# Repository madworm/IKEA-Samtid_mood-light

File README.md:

IKEA-Samtid_mood-light
======================

LAYOUT FILES: Circular extension board for IKEA Samtid lamps (*).

WS2812B-based Arduino compatible RGB ring light. 

Remote control with:

* HC-05 bluetooth module (native).
* ESP8266 with adapter PCB & 3.3V regulator (small adapter).

Hardware releases: 

* [V0.27.a](https://github.com/madworm/IKEA-Samtid_mood-light/releases/tag/V0.27.a): basic mood light
* [Final](https://github.com/madworm/IKEA-Samtid_mood-light/releases/tag/Final): upgraded with Bluetooth/WiFi option

See 'Docs' on master branch for hints/errata!

Firmware [repository](https://github.com/madworm/IKEA-Samtid_mood-light_FW) & Arduino setup files.
Works with Adafruit [NeoPixel](https://github.com/adafruit/Adafruit_NeoPixel) library.

(*) I was told it also works with IKEA Aläng lamps.

---

Created with KiCad BZR5093 or later. You need an up-to-date release to open these files!

Before having PC-boards made, please make sure you know about your manufacturer's peculiarities!
Especially drill-sizes and their tolerances may vary too much and give you trouble.

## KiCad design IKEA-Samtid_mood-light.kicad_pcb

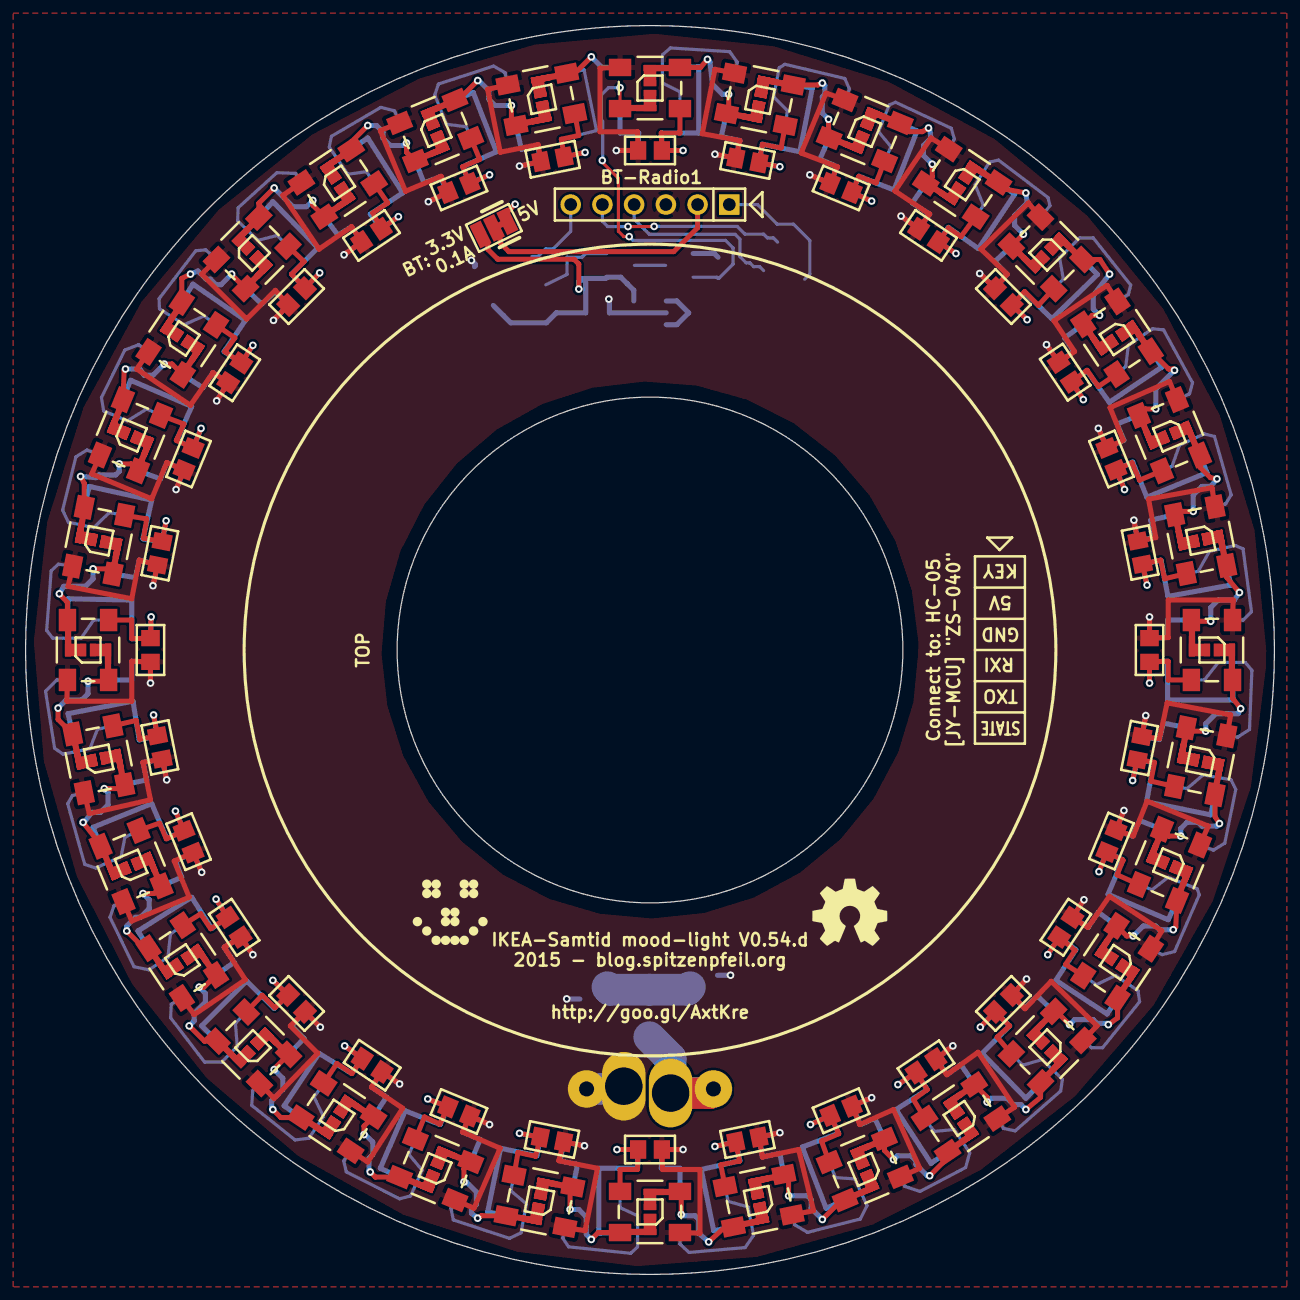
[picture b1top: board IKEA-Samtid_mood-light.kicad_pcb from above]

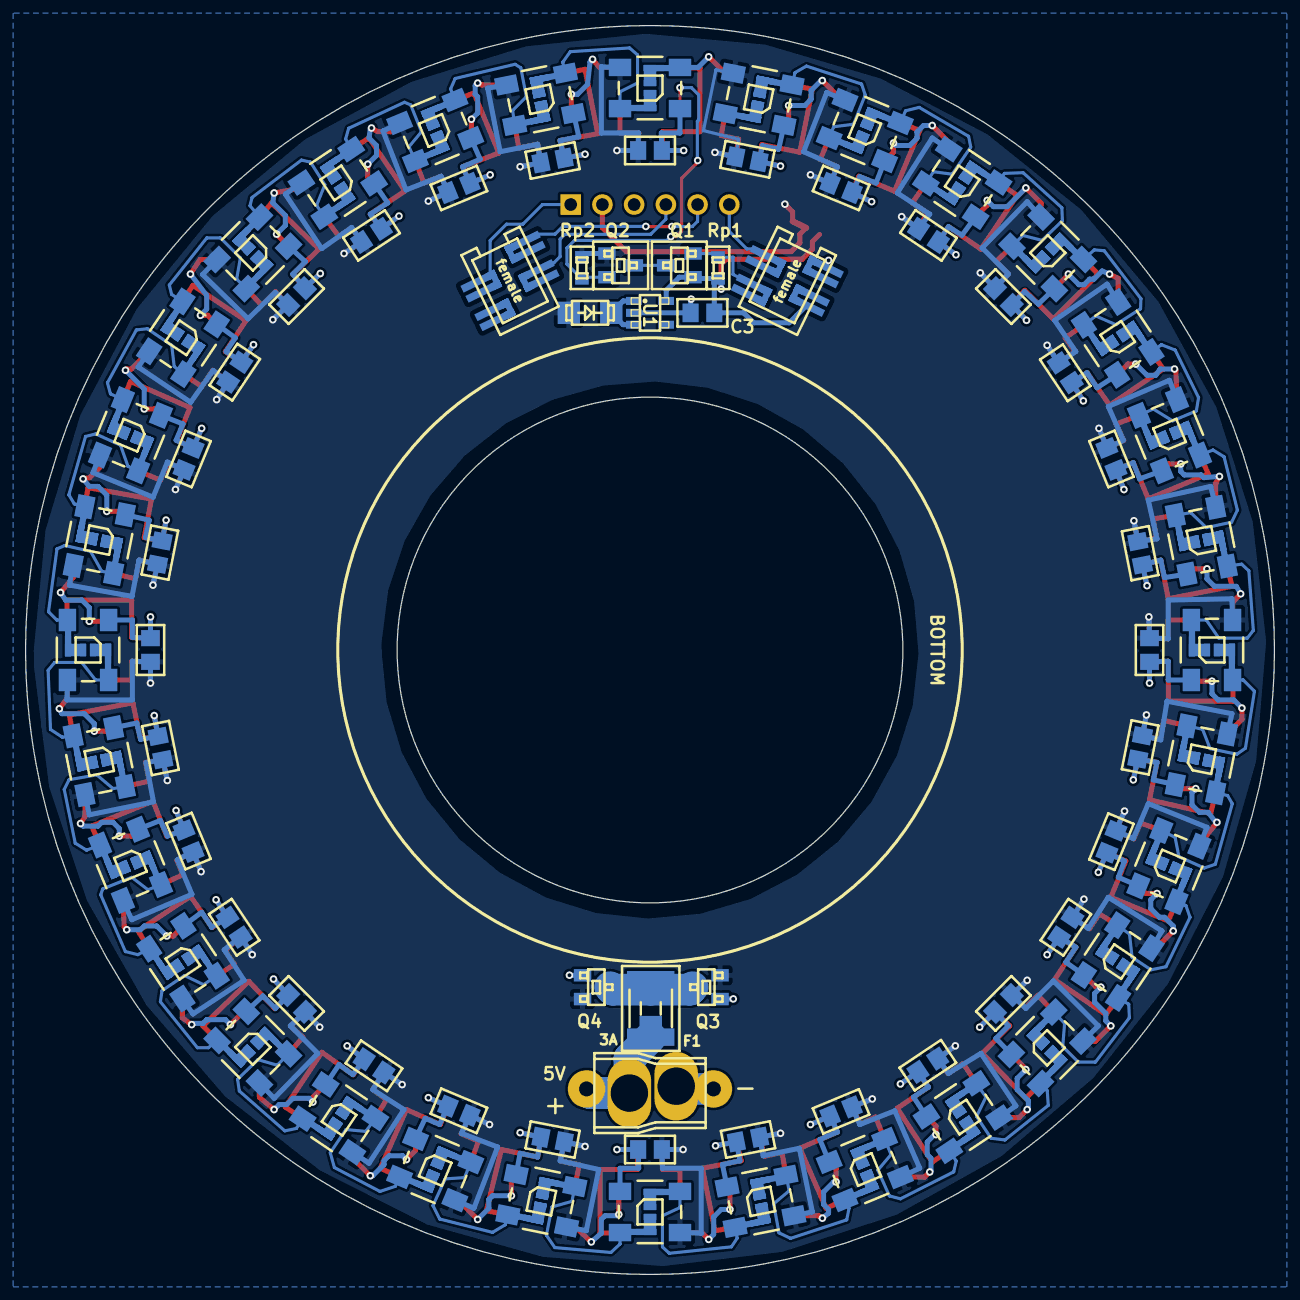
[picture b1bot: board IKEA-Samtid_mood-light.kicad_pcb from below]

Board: 2 copper layers, 100.0 x 100.0 mm, 146 parts (77 on the bottom side), 77 nets.

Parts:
BT-Radio1: HC-05; SIL-6
C3, C5, C6, C7, C8, C9, C10, C11, C12, C13, C14, C15, C16, C17, C18, C19, C20, C21, C22, C23, C24, C25, C26, C27, C28, C29, C30, C31, C32, C33, C34, C35, C36, C37, C38, C39, C40, C41, C42, C43, C44, C45, C46, C47, C48, C49, C50, C51, C52, C53, C54, C55, C56, C57, C58, C59, C60, C61, C62, C63, C64, C65, C66, C67, C68: 1µF; MADW__C0805
DS1: SS14L; MADW__diode_sub-SMA
F1: 3A-poly; SM1812_1206
JP3: BT:5V(3.3); SMD-solder-bridge-3pin
LED1, LED2, LED3, LED4, LED5, LED6, LED7, LED8, LED9, LED10, LED11, LED12, LED13, LED14, LED15, LED16, LED17, LED18, LED19, LED20, LED21, LED22, LED23, LED24, LED25, LED26, LED27, LED28, LED29, LED30, LED31, LED32, LED33, LED34, LED35, LED36, LED37, LED38, LED39, LED40, LED41, LED42, LED43, LED44, LED45, LED46, LED47, LED48, LED49, LED50, LED51, LED52, LED53, LED54, LED55, LED56, LED57, LED58, LED59, LED60, LED61, LED62, LED63, LED64: WS2812B; WS2812B_data-bridgeable
LOGO1: LED_smile_silkscreen_6mm
LOGO2: OSHW-logo_silkscreen_6mm
P2: POWER; Deans_mini-T_male
P3: POWER; Socket_MOLEX-KK-RM2-54mm_Lock_5pin_straight
P3.1: B-to-B-1A; 0-188275-4_SMD_4-pin_female_split-pads
P4.1: B-to-B-2A; 0-188275-4_SMD_4-pin_female_split-pads
Q1, Q2: BSS138; MADW__SOT23
Q3, Q4: IRLML6401PbF; MADW__SOT23
Rp1, Rp2: 1k5; MADW__R0603_2
U1: AP2204K-SOT23-5; MADW__SOT23-5

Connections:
+5V: C5.1, C6.1, C7.1, C8.1, C9.1, C10.1, C11.1, C12.1, C13.1, C14.1, C15.1, C16.1, C17.1, C18.1, C19.1, C20.1, C21.1, C22.1, C23.1, C24.1, C25.1, C26.1, C27.1, C28.1, C29.1, C30.1, C31.1, C32.1, C33.1, C34.1, C35.1, C36.1, C37.1, C38.1, C39.1, C40.1, C41.1, C42.1, C43.1, C44.1, C45.1, C46.1, C47.1, C48.1, C49.1, C50.1, C51.1, C52.1, C53.1, C54.1, C55.1, C56.1, C57.1, C58.1, C59.1, C60.1, C61.1, C62.1, C63.1, C64.1, C65.1, C66.1, C67.1, C68.1, DS1.1, JP3.1, LED1.1, LED2.1, LED3.1, LED4.1, LED5.1, LED6.1, LED7.1, LED8.1, LED9.1, LED10.1, LED11.1, LED12.1, LED13.1, LED14.1, LED15.1, LED16.1, LED17.1, LED18.1, LED19.1, LED20.1, LED21.1, LED22.1, LED23.1, LED24.1, LED25.1, LED26.1, LED27.1, LED28.1, LED29.1, LED30.1, LED31.1, LED32.1, LED33.1, LED34.1, LED35.1, LED36.1, LED37.1, LED38.1, LED39.1, LED40.1, LED41.1, LED42.1, LED43.1, LED44.1, LED45.1, LED46.1, LED47.1, LED48.1, LED49.1, LED50.1, LED51.1, LED52.1, LED53.1, LED54.1, LED55.1, LED56.1, LED57.1, LED58.1, LED59.1, LED60.1, LED61.1, LED62.1, LED63.1, LED64.1, Q2.1, Q3.2, Q4.2, Rp2.1
/5V_raw: F1.2, P2.2, P3.5
/KEY.A: BT-Radio1.1, P4.1.2
/LEDS.A: P3.1.4, Q1.2, Rp1.2
/RXI.A: BT-Radio1.4, P4.1.3
/STATE.A: BT-Radio1.6, P3.1.2
/TXO.A: BT-Radio1.5, P4.1.1
/VCC.A: C3.1, JP3.3, P3.1.3, Q1.1, Rp1.1, U1.5
/WS2812B-LEDs-1/A_IN: LED1.4, Q2.2, Rp2.2
/WS2812B-LEDs-1/A_OUT: LED8.2, LED9.4
/WS2812B-LEDs-1/B_OUT: LED16.2, LED17.4
/WS2812B-LEDs-1/C_OUT: LED24.2, LED25.4
/WS2812B-LEDs-1/D_OUT: LED32.2, LED33.4
/WS2812B-LEDs-1/GND: BT-Radio1.3, C3.2, C5.2, C6.2, C7.2, C8.2, C9.2, C10.2, C11.2, C12.2, C13.2, C14.2, C15.2, C16.2, C17.2, C18.2, C19.2, C20.2, C21.2, C22.2, C23.2, C24.2, C25.2, C26.2, C27.2, C28.2, C29.2, C30.2, C31.2, C32.2, C33.2, C34.2, C35.2, C36.2, C37.2, C38.2, C39.2, C40.2, C41.2, C42.2, C43.2, C44.2, C45.2, C46.2, C47.2, C48.2, C49.2, C50.2, C51.2, C52.2, C53.2, C54.2, C55.2, C56.2, C57.2, C58.2, C59.2, C60.2, C61.2, C62.2, C63.2, C64.2, C65.2, C66.2, C67.2, C68.2, LED1.3, LED2.3, LED3.3, LED4.3, LED5.3, LED6.3, LED7.3, LED8.3, LED9.3, LED10.3, LED11.3, LED12.3, LED13.3, LED14.3, LED15.3, LED16.3, LED17.3, LED18.3, LED19.3, LED20.3, LED21.3, LED22.3, LED23.3, LED24.3, LED25.3, LED26.3, LED27.3, LED28.3, LED29.3, LED30.3, LED31.3, LED32.3, LED33.3, LED34.3, LED35.3, LED36.3, LED37.3, LED38.3, LED39.3, LED40.3, LED41.3, LED42.3, LED43.3, LED44.3, LED45.3, LED46.3, LED47.3, LED48.3, LED49.3, LED50.3, LED51.3, LED52.3, LED53.3, LED54.3, LED55.3, LED56.3, LED57.3, LED58.3, LED59.3, LED60.3, LED61.3, LED62.3, LED63.3, LED64.3, P2.1, P3.1, P3.1.1, Q3.1, Q4.1, U1.2
/WS2812B-LEDs-2/E_OUT: LED40.2, LED41.4
/WS2812B-LEDs-2/F_OUT: LED48.2, LED49.4
/WS2812B-LEDs-2/G_OUT: LED56.2, LED57.4
unnamed: BT-Radio1.2, JP3.2
unnamed: DS1.2, U1.1, U1.3
unnamed: F1.1, Q3.3, Q4.3
unnamed: LED1.2, LED2.4
unnamed: LED2.2, LED3.4
unnamed: LED3.2, LED4.4
unnamed: LED4.2, LED5.4
unnamed: LED5.2, LED6.4
unnamed: LED6.2, LED7.4
unnamed: LED7.2, LED8.4
unnamed: LED10.2, LED11.4
unnamed: LED9.2, LED10.4
unnamed: LED11.2, LED12.4
unnamed: LED12.2, LED13.4
unnamed: LED13.2, LED14.4
unnamed: LED14.2, LED15.4
unnamed: LED15.2, LED16.4
unnamed: LED17.2, LED18.4
unnamed: LED18.2, LED19.4
unnamed: LED19.2, LED20.4
unnamed: LED20.2, LED21.4
unnamed: LED21.2, LED22.4
unnamed: LED22.2, LED23.4
unnamed: LED23.2, LED24.4
unnamed: LED25.2, LED26.4
unnamed: LED26.2, LED27.4
unnamed: LED27.2, LED28.4
unnamed: LED28.2, LED29.4
unnamed: LED29.2, LED30.4
unnamed: LED30.2, LED31.4
unnamed: LED31.2, LED32.4
unnamed: LED33.2, LED34.4
unnamed: LED34.2, LED35.4
unnamed: LED35.2, LED36.4
unnamed: LED36.2, LED37.4
unnamed: LED37.2, LED38.4
unnamed: LED38.2, LED39.4
unnamed: LED39.2, LED40.4
unnamed: LED41.2, LED42.4
unnamed: LED42.2, LED43.4
unnamed: LED43.2, LED44.4
unnamed: LED44.2, LED45.4
unnamed: LED45.2, LED46.4
unnamed: LED46.2, LED47.4
unnamed: LED47.2, LED48.4
unnamed: LED49.2, LED50.4
unnamed: LED50.2, LED51.4
unnamed: LED51.2, LED52.4
unnamed: LED52.2, LED53.4
unnamed: LED53.2, LED54.4
unnamed: LED54.2, LED55.4
unnamed: LED55.2, LED56.4
unnamed: LED57.2, LED58.4
unnamed: LED58.2, LED59.4
unnamed: LED59.2, LED60.4
unnamed: LED60.2, LED61.4
unnamed: LED61.2, LED62.4
unnamed: LED62.2, LED63.4
unnamed: LED63.2, LED64.4
unnamed: Q1.3, Q2.3

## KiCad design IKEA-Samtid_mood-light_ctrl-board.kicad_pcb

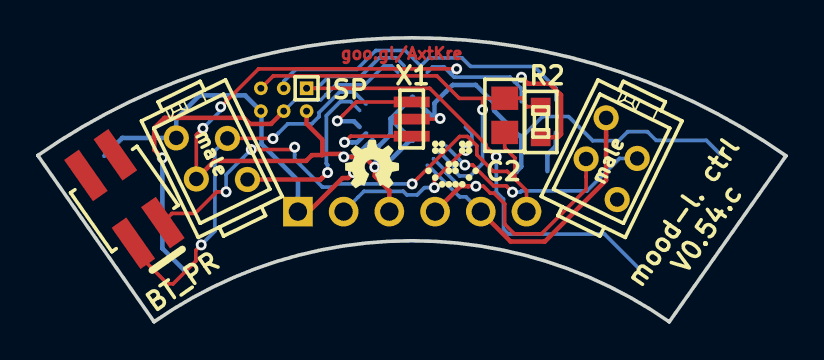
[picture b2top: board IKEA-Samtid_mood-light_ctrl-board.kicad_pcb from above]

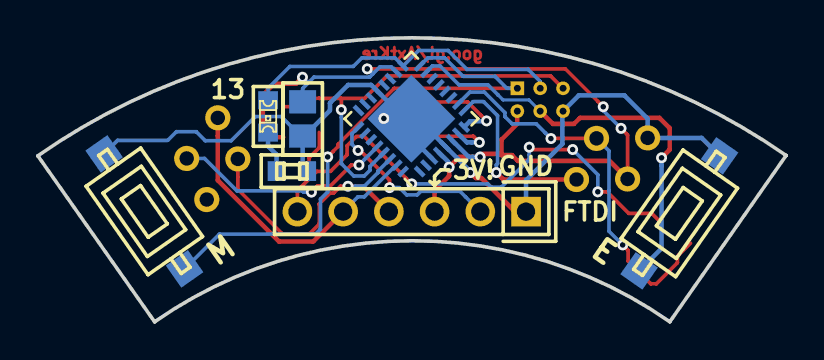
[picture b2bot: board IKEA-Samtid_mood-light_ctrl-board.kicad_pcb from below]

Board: 2 copper layers, 41.6 x 15.8 mm, 16 parts (7 on the bottom side), 16 nets.

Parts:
C1: 1µF; MADW__C0805
C2: 1nF-ish; MADW__C0805
IC1: ATMEGA168PA-M; QFN-32-1EP_5x5mm_Pitch0.5mm
JP1: AVR_ISP; MADW__PIN_ARRAY_3x2_1.27mm
JP2: BT-PROG_EN; DIL-2-2.00mm_male_vert_SMD_PH2M15-2XX-U
LED65: LED; MADW__CHIPLED-0603
LOGO1: LED_smile_silkscreen_3mm
LOGO2: OSHW-logo_silkscreen_3mm
P1: FTDI; MADW__SIL-6
P3.2: B-to-B-1B; 0-215464-4_TH_4-pin_male
P4.2: B-to-B-2B; 0-215464-4_TH_4-pin_male
R1: 1k; MADW__R0603_2
R2: 10k; MADW__R0603_2
SW1: ENTER; MADW__push-button-SMD-3.7x6.0
SW2: MODE; MADW__push-button-SMD-3.7x6.0
X1: CSTCE16M0V53-R0; MADW__murata-resonator__CSTCE16M0V53-R0

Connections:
/ADC2: IC1.25, P1.2
/DTR.B: C2.1, JP2.2, P1.6
/GND.B: C1.2, IC1.3, IC1.5, IC1.21, IC1.33, JP1.6, P1.1, P3.2.1, R1.2, SW1.2, SW2.2, X1.2
/KEY.B: IC1.28, P4.2.2
/LEDS.B: IC1.9, P3.2.4
/MISO: IC1.16, JP1.1, SW2.1
/MOSI: IC1.15, JP1.4, SW1.1
/RST: C2.2, IC1.29, JP1.5, R2.2
/RXI.B: IC1.30, P1.4, P4.2.3
/SCK: IC1.17, JP1.3, LED65.1
/STATE.B: IC1.10, JP2.1, P3.2.2
/TXO.B: IC1.31, P1.5, P4.2.1
/VCC.B: C1.1, IC1.4, IC1.6, IC1.18, JP1.2, P1.3, P3.2.3, R2.1
/XTAL1: IC1.7, X1.1
/XTAL2: IC1.8, X1.3
unnamed: LED65.2, R1.1

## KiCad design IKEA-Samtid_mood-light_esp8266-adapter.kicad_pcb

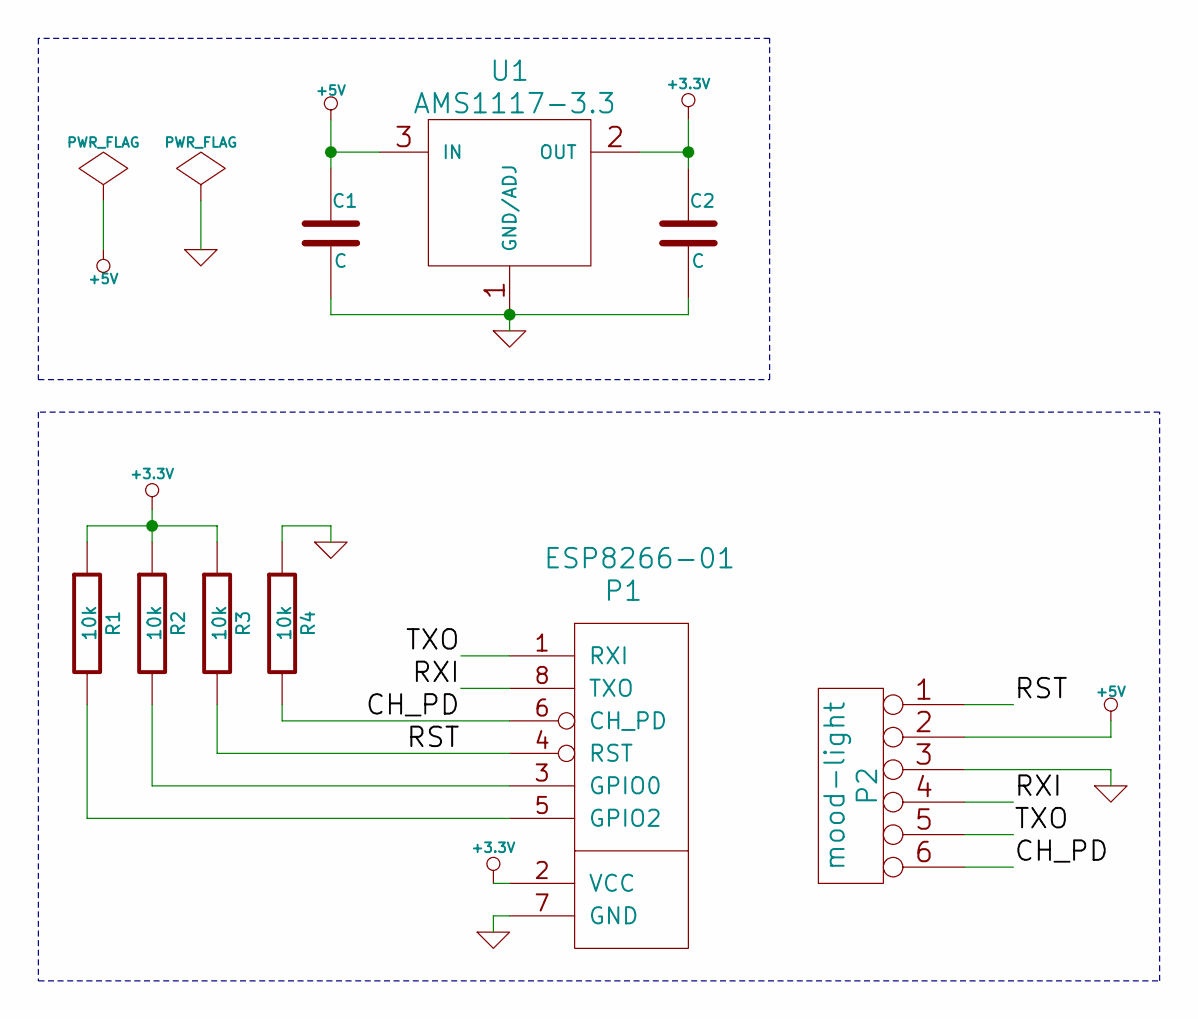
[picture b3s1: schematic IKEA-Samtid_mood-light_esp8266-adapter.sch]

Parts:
C1, C2: C; MADW__C0805
P1: ESP8266-01; DIL-4
P2: mood-light; SIL-6
R1, R2, R3, R4: 10k; MADW__R0603_2
U1: AMS1117-3.3; SOT-223

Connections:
+3.3V: C2.1, P1.2 (VCC), R1.1, R2.1, R3.1, U1.2 (OUT)
+5V: C1.1, P2.2, U1.3 (IN)
/CH_PD: P1.6 (CH_PD), P2.6, R4.2
/RST: P1.4 (RST), P2.1, R3.2
/RXI: P1.1 (RXI), P2.5
/TXO: P1.8 (TXO), P2.4
GND: C1.2, C2.2, P1.7 (GND), P2.3, R4.1, U1.1 (GND/ADJ)
unnamed: P1.3 (GPIO0), R2.2
unnamed: P1.5 (GPIO2), R1.2

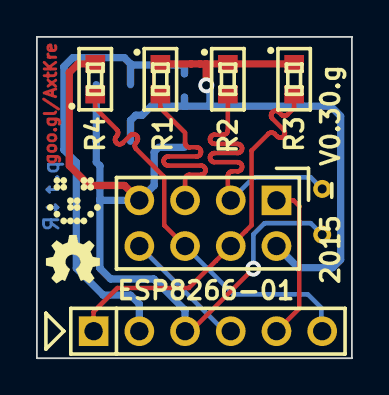
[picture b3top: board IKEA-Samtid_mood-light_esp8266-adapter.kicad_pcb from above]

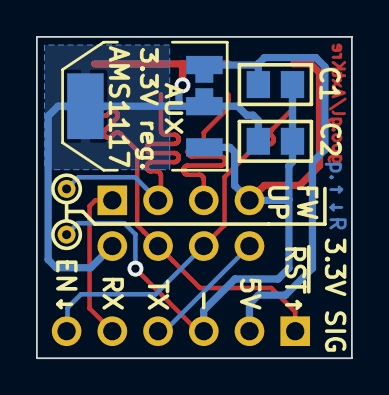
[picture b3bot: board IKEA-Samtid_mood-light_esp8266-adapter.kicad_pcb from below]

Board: 2 copper layers, 17.5 x 17.8 mm, 11 parts (3 on the bottom side), 9 nets.

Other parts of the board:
G1: OSHW-logo_silkscreen_3mm
G2: LED_smile_silkscreen_3mm

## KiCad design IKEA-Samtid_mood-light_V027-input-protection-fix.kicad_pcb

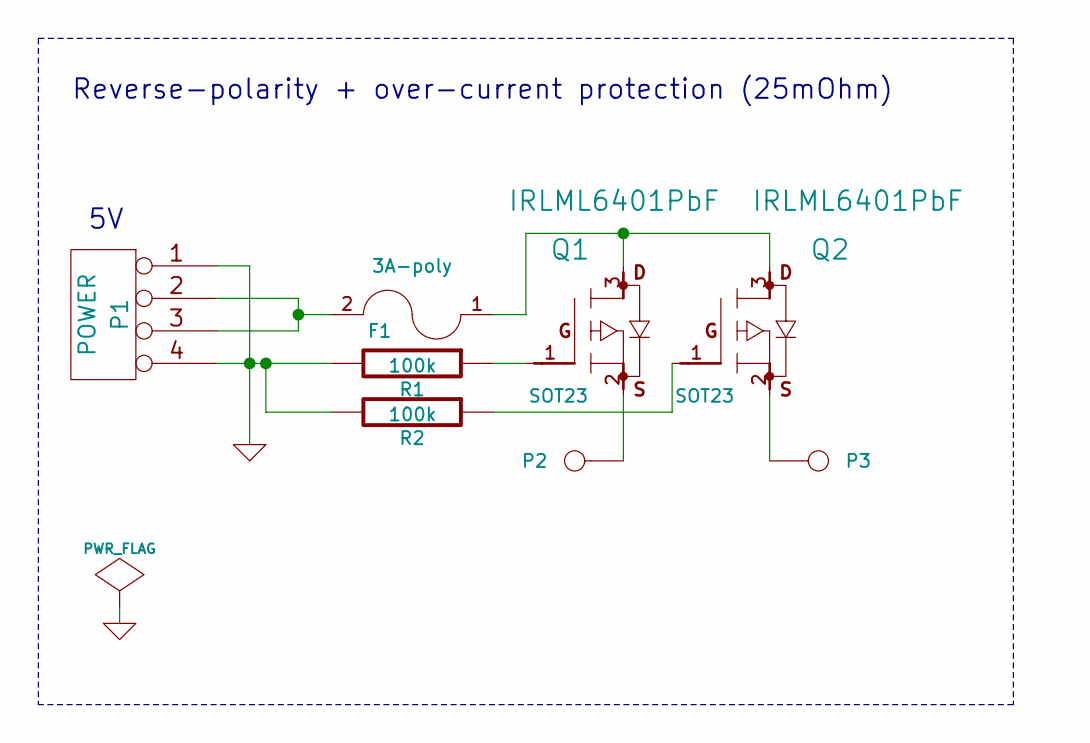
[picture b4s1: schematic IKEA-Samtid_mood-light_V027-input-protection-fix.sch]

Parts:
F1: 3A-poly
P1: POWER
P2, P3: CONN_1
Q1, Q2: IRLML6401PbF; SOT23
R1, R2: 100k

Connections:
GND: P1.1, P1.4, R1.2, R2.2
unnamed: F1.1, Q1.3 (D), Q2.3 (D)
unnamed: F1.2, P1.2, P1.3
unnamed: P2.1, Q1.2 (S)
unnamed: P3.1, Q2.2 (S)
unnamed: Q1.1 (G), R1.1
unnamed: Q2.1 (G), R2.1

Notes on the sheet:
Reverse-polarity + over-current protection (25mOhm)

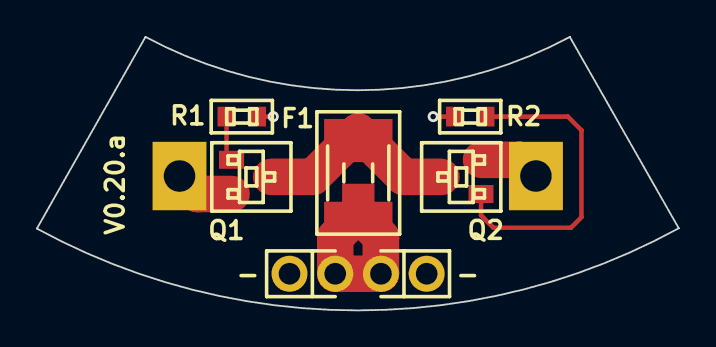
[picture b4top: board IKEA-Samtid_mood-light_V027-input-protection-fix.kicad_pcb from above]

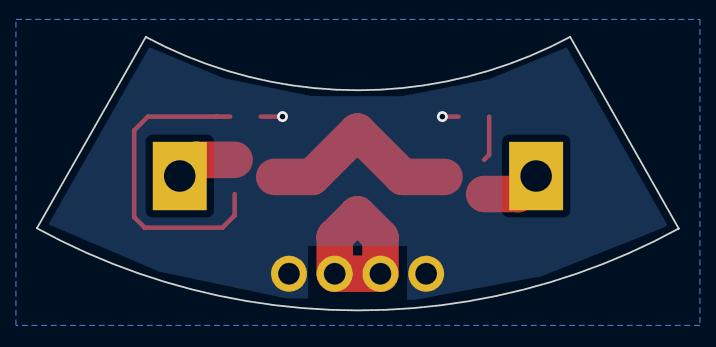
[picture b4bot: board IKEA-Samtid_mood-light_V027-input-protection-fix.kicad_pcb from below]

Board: 2 copper layers, 35.7 x 15.2 mm, 8 parts (2 on the bottom side), 7 nets.

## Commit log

2014-07-08 Stuff.
2014-07-08 More stuff.
2014-07-08 Trying to be creative.
2014-07-10 Adding WS2812B footprints for testing board real-estate.
2014-07-10 Made schematic + placing a couple of LEDs.
2014-07-10 First serious attempt at routing the board. No fun so far.
2014-07-10 Rotate LEDs 90°. Might help with routing a bit.
2014-07-10 Limiting tracks to 45° is crap for circular boards. Looks horrible.
2014-07-11 Tracks...
2014-07-11 This is getting very tedious.
2014-07-11 Renamed repository + files --> 'IKEA-Samtid_mood-light'.
2014-07-11 Added some measurements.
2014-07-11 Sucks that KiCad doesn't support object grouping and other CAD essentials.
2014-07-11 Large circular boards suck without decent CAD features in software.
2014-07-11 Done placing the LEDs (phew). Now some routing.
2014-07-11 KiCad seriously needs: route segment + proper copy / transform + paste.
2014-07-11 Routed all LEDs + their caps. Never again... Next: micro + POWER.
2014-07-11 Playing with copper pour.
2014-07-12 Not enough free space for FTDI header :-(
2014-07-12 Had to move micro to daughter-board. Nasty routing-path creation.
2014-07-12 Schematic: forgot change of 'TQFP-32' --> 'QFN32' for micro.
2014-07-12 Messing with µC board. Not so easy without board space.
2014-07-12 Getting there...
2014-07-13 Put 150R in LED data line.
2014-07-13 Using board-to-board connectors (micro-Match).
2014-07-13 Getting lost in hirarchical schematic sheets...
2014-07-13 Hirarchical schem. sheets have 'interesting' effects on net-names.
2014-07-13 Power connector done.
2014-07-14 Might be the first prototype.
2014-07-14 Added a warning regarding the SMD micor-Match footprints.
2014-07-14 Used my own FP for the female SMD micro-Match connector. Need to verify.
2014-07-14 Added part numbers for the micro-Match connectors.
2014-07-14 2x dual poly-switch fuse footprint: 1206/1812 + tweaks. Can't use 4A TH.
2014-07-15 Changed main Schottky to SK84B (beefier, bigger package, SMC).
2014-07-15 Tweaked copper pour around the 'fat' Schottky diode.
2014-07-18 Used [experimental] micro-MaTch footprint with split pads.
2014-07-19 Added spacer board.
2014-07-19 Silkscreen tweaks.
2014-07-20 Updated the spacer board outline.
2014-07-23 Updated female micro-MaTch (SMD) footprints. Silkscreen was off a bit.
2014-07-23 Updated male micro-MaTch (TH) footprints.
2014-07-23 Tweaks.
2014-07-23 More tweaks.
2014-07-23 Tweaked the vias.
2014-07-24 Trying to swap male / female micro-MaTch connectors.
2014-07-24 Swapped male / female micro-MaTch connectors. Adjusted spacer board.
2014-07-24 Sanity checking + tweaks here and there.
2014-07-24 Removed a lot of INSANE vias.
2014-07-24 Made a trace thicker, as it might see some mechanical stress.
2014-07-24 Moved DS2 to a much better place.
2014-07-25 Added a status LED.
2014-07-25 Tweaked some tracks around a via. Not enough clearance.
2014-07-25 Had the pull-up voltages reversed on the MOSFET isolator.
2014-07-25 Massive silkscreen cleanup + tweaks. Power-connector larger holes.
2014-07-26 Changed pull-up resistors to 1.5k. Roughly following: (VCC-0.4)/0.003
2014-07-26 Changed SOT23 MOSFET footprints: D-S bridgeable.
2014-07-26 A bit more copper-pour pullback from the center hole.
2014-07-26 Routed ADC2 to pin #2 of the FTDI connector.
2014-07-28 ISP header tweaks.
2014-07-28 Added a 100nF cap between DTR and RST ("auto-reset").
2014-07-28 Silkscreen tweaks. I need to make up my mind about this stuff.
2014-08-01 Had to split the project into two separate ones.
    * LED board
    * Control board
    The PCB-fab doesn't like one layout with "board-in-board".
2014-08-04 Went back to just 1 schematic file.
2014-08-15 Added 'hints.txt' with stuff I found worth writing down.
2014-08-16 Updated 'hints.txt'.
2014-08-16 Added BOM file.
2014-08-17 Updated 'README.md'.
2014-08-17 Added an image.
2014-08-17 Updated female microMaTch footprint (split-pads stop-mask removed).
2014-08-23 Found & fixed auto-reset issue running 5V. 3.3V worked all the time.
    Had to add 100k across the auto-reset capacitor C1.
2014-08-23 Upgraded all files to V0.28 / V0.28.a (5V auto-reset fix).
2014-08-24 Fixed brd outline issue on control board (nodes too far apart for 3D view).
2014-08-24 Larger ctrl-board to remove interf. of switch <-> microMaTch - (V0.28.b).
2014-08-24 Tweaked ctrl-board a bit.
2014-08-24 Reverse-polarity protection: replaced SK84 with 2x p-ch mosfets.
2014-08-24 Added input-protection upgrade board for V0.27 boards.
2014-08-25 1x 3A poly-fuse is enough (just 20mOhm @ 2.6A).
2014-08-25 Updated ...BOM.txt
2014-08-25 Tweaked input prot. circ. layout (easy solder bridges if not needed).
2014-08-25 One 3A poly-switch is enough: input-protection upgrade board for V0.27 boards.
2014-09-01 Updated 'ERRATA.txt' and 'hints.txt'.
2014-09-02 Added a pdf to print out a template for the spacer board.
2014-09-02 Recreated some PNG images.
2014-09-03 Corrected board version # to V0.31.b.
    Was erroneously set to V0.32.a in commit 87c96148e440df0fed2edb802d3d12295cd7b7d9.
2014-09-03 Rerouted ctrl-board. Programming header moved to safe location.
2014-09-04 Ctrl-board: layout tweaks (tracks further away from board edge).
2014-09-27 Updated the errata file.
2014-09-29 Moved 'hints' and 'ERRATA' to 'Docs' folder.
2014-11-02 Added WS2812B datasheet (with reflow info).
2014-11-17 Added digikey + ebay info regarding SMD button-switch to BOM.
2015-01-05 Added images to 'Docs'.
2015-01-05 Renamed a file.
2015-01-14 Tweaked power connection on main board --> V0.31.c
2015-01-14 Forgot to change image name in 'README.md'.
2015-01-15 Updated some PNGs.
2015-01-21 Corrected a number.
2015-02-01 Added some notes.
2015-02-02 Being creative...
2015-02-02 Switched to SIL-6 connector for HC-05 (vertically mounted).
2015-02-03 Added decoupling cap for 3.3V reg.
2015-02-03 180-d the microMaTch connectors to prevent plugging in old boards.
2015-02-03 Playing with HC-05 placement.
2015-02-03 HC-05 tweaks. Forgot about on-board 3.3V regulator.
2015-02-03 Added info for alternative 3.3V regulator.
2015-02-03 Added a note to 'Docs' folder.
2015-02-04 Replaced 'auto-reset' capacitor with 1nF.
2015-02-04 Removed 'bleeder' resistor on auto-reset capacitor, replaced with 10k pull-up for reset.
    Auto reset works with:
    * FTDI cable
    * other FTDI-based adapter
    * HC-05 Bluetooth module (most of the time)
2015-02-05 Simplifications.
2015-02-05 Shoved a few traces around (ctrl board).
2015-02-05 Playing with mini-T power connector. Feasibility test.
2015-02-05 Ctrl-board tweaks.
2015-02-05 Rerouted the ctrl-board.
2015-02-06 Added photos of 'my' HC-05 module to 'Docs' folder.
2015-02-06 Moved DS1 from ctrl-board to main board (before 3.3V reg)
    --> correct pull-up voltage on level-shifter (== VCC of micro).
2015-02-06 Some cleanup. Still need to fix the power connector(s).
2015-02-07 Shifted traces around. The P&S router sometimes does strange things.
2015-02-12 Added Deans mini-T power connector. It fits! Might be ready now.
2015-02-16 Added solder-bridge to enable/disable remote programming via BT.
2015-02-21 Replaced BT solder bridge with 1.27mm jumper.
2015-02-25 Layout tweaks.
2015-02-25 Removed obsolete stuff.
2015-02-27 Changed BT jumper to 2.00mm one. Much easier to get.
2015-03-06 Made ctrl-board some 0.1mm wider (radially) --> no traces near edge.
2015-03-09 Added alternative footprint for power input (5-pin Molex KK).
2015-03-09 Updated BOM file + other very minor stuff.
2015-03-10 Added alternative part for p-ch MOSFETS.
2015-03-11 Updated BOM file.
2015-03-11 Added a solder bridge for 5V(3.3) selection for BT module.
2015-03-11 Solder mask tweaks (BT V-sel).
2015-03-11 Moved V-sel. jumper to outside of top keepout zone.
2015-03-12 First draft of ESP8266 adapter board (incl. 3.3V reg).
2015-03-12 ESP8266 adapter board reduced in size.
2015-03-12 ESP8266 adapter tweaks.
2015-03-13 Added pads for ESP8266 FW upd. mode (GPIO0 shorted to GND) on startup.
2015-03-13 ESP8266 adapter: changed RX/TX netnames to avoid confusion.
2015-03-13 Swapped RXI/TXO for HC-05 module on silkscreen.
    Now represents what the main-board wants, not what HC-05 provides.
2015-03-13 ESP8266 adapter: silkscreen tweaks (show pull-up/down status).
2015-03-13 ESP8266 adapter tweaks + added shortened github link on copper.
2015-03-13 Added shortened github link to main board as well.
2015-03-13 Added shortened github link to ctrl board.
2015-03-14 ESP8266 adapter: played with trace length tuning a bit (just for fun).
2015-03-14 ESP8266 adapter: Added 3D model.
2015-03-14 ESP8266 adapter: added 3D model for SOT-223 part.
2015-03-14 ESP8266 adapter: updated 3D shapes to ch. in github kicad libraries.
2015-03-15 ESP8266 adapter: added a bit of copper pour as heatsink.
2015-03-16 ESP8266 adapter: tweaks.
2015-03-19 ESP8266 adapter: moved FW-UP pins to more convenient spot.
2015-03-19 CTRL-board: fixed DRC clearance violation (harmless) of text on copper layer.
2015-03-19 CTRL-board: minor tweaks (silk + copper).
2015-03-20 Main-board: silkscreen tweaks (avoid via).
2015-03-21 Added stuff to 'Docs' folder.
2015-03-21 Added ctrl-board stuff to 'Docs'.
2015-03-21 Updated ESP8266 stuff in 'Docs'.
2015-03-21 Changed voltage rating of C2 to 50V (10V too low).
2015-03-22 Added LED-board stuff to 'Docs'
2015-04-14 Updated 'hints.txt': soldering temperature for WS2812B.
2015-04-15 Updated PNG images.
2015-04-29 Updated 'hints.txt' with info on possible WS2812B issues & how to identify them.
2015-04-30 Moved WS2812B datasheet to 'LED-board' folder where it belongs.
2015-05-04 Updated 'README.md' (releases).
2015-06-18 Updated comment about MCU RAM usage.
